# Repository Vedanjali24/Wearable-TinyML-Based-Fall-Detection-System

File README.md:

# Wearable-TinyML-Based-Fall-Detection-System
This project focuses on the design and development of a wearable health monitoring system capable of performing real-time motion analysis and fall detection directly on the device. The system is built around the ESP32 microcontroller, which serves as the main processing unit for sensor data acquisition, TinyML inference, and data logging.

The device integrates an MPU6050 inertial measurement unit (IMU) to capture motion and orientation data and a MAX30102 optical sensor for physiological monitoring such as heart rate and blood oxygen levels. Motion data from the IMU is processed locally using a TinyML model trained for fall detection, allowing the system to identify abnormal movement patterns without requiring external computation resources.

To enable reliable data storage and post-analysis, the system includes SD card logging, where raw sensor readings and detected events are stored during operation. This allows offline analysis of movement patterns, model performance evaluation, and long-term monitoring.

A key objective of the system is privacy-preserving edge intelligence. All inference and decision-making are performed directly on the embedded device, eliminating the need for continuous cloud connectivity. This reduces latency, lowers power consumption, and ensures that sensitive health data remains local to the device.

The combination of embedded machine learning, sensor fusion, and edge processing enables the device to operate as a compact and efficient health monitoring platform capable of detecting potential falls and anomalies in real time.

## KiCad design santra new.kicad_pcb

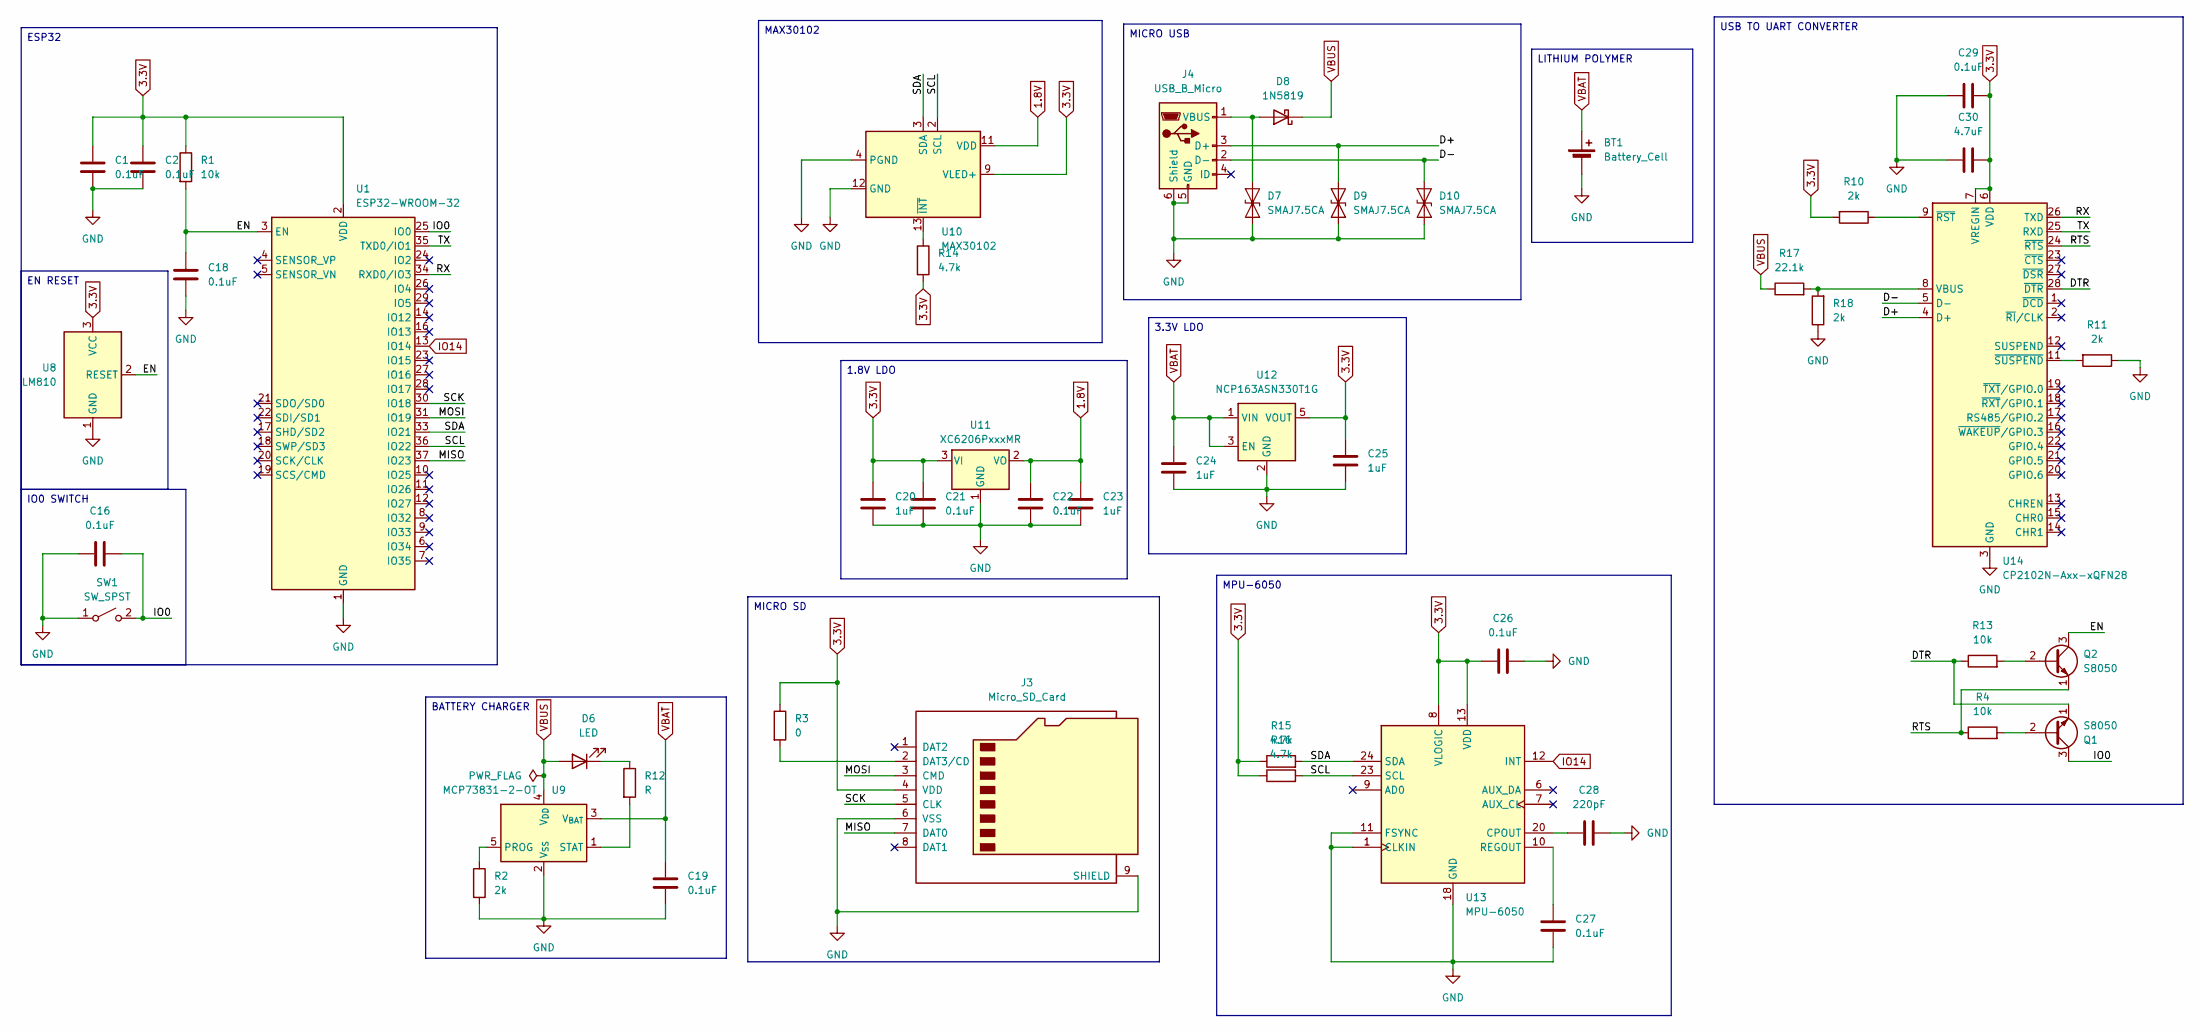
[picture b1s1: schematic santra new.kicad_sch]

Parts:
BT1: Battery_Cell; LED_PLCC-2_3x2mm_AK
C1, C2, C16, C18, C19, C21, C22, C26, C27, C29: 0.1uF; C_0603_1608Metric_Pad1.08x0.95mm_HandSolder
C20, C23, C24, C25: 1uF; C_0603_1608Metric_Pad1.08x0.95mm_HandSolder
C28: 220pF; C_0603_1608Metric_Pad1.08x0.95mm_HandSolder
C30: 4.7uF; C_0603_1608Metric_Pad1.08x0.95mm_HandSolder
D6: LED; LED_0603_1608Metric_Pad1.05x0.95mm_HandSolder
D7, D9, D10: SMAJ7.5CA; D_SMA
D8: 1N5819; D_DO-41_SOD81_P10.16mm_Horizontal
J3: Micro_SD_Card; microSD_HC_Molex_47219-2001
J4: USB_B_Micro; USB_Micro-B_Molex-105017-0001
Q1, Q2: S8050; Texas_DRT-3
R1, R4, R13: 10k; R_0603_1608Metric_Pad0.98x0.95mm_HandSolder
R2, R10, R11, R18: 2k; R_0603_1608Metric_Pad0.98x0.95mm_HandSolder
R3: 0; R_0603_1608Metric_Pad0.98x0.95mm_HandSolder
R12: R; R_0603_1608Metric_Pad0.98x0.95mm_HandSolder
R14, R15, R16: 4.7k; R_0603_1608Metric_Pad0.98x0.95mm_HandSolder
R17: 22.1k; R_0603_1608Metric_Pad0.98x0.95mm_HandSolder
SW1: SW_SPST; SW_Push_1P1T_NO_CK_PTS125Sx43PSMTR
U1: ESP32-WROOM-32
U8: LM810; SOT-23
U9: MCP73831-2-OT; SOT-23-5
U10: MAX30102; Maxim_OLGA-14_3.3x5.6mm_P0.8mm
U11: XC6206PxxxMR; SOT-23-3
U12: NCP163ASN330T1G; SOT-23-5
U13: MPU-6050; InvenSense_QFN-24_4x4mm_P0.5mm
U14: CP2102N-Axx-xQFN28; QFN-28-1EP_5x5mm_P0.5mm_EP3.35x3.35mm

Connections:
1.8V: C22.1, C23.1, U10.11 (VDD), U11.2 (VO)
3.3V: C1.1, C2.1, C20.1, C21.1, C25.1, C26.1, C29.2, C30.2, J3.4 (VDD), R1.1, R3.1, R10.2, R14.2, R15.1, R16.1, U1.2 (VDD), U8.3 (VCC), U10.9 (VLED+), U10.10 (VLED+), U11.3 (VI), U12.5 (VOUT), U13.8 (VLOGIC), U13.13 (VDD), U14.6 (VDD), U14.7 (VREGIN)
/D+: D9.2 (A2), J4.3 (D+), U14.4 (D+)
/D-: D10.2 (A2), J4.2 (D-), U14.5 (D-)
/DTR: Q1.1 (E), R13.1, U14.28 (~DTR)
/EN: C18.1, Q2.3 (C), R1.2, U1.3 (EN), U8.2 (RESET)
/IO0: C16.2, Q1.3 (C), SW1.2 (B), U1.25 (IO0)
/MISO: J3.7 (DAT0), U1.37 (IO23)
/MOSI: J3.3 (CMD), U1.31 (IO19)
/RTS: Q2.1 (E), R4.1, U14.24 (~RTS)
/RX: U1.34 (RXD0/IO3), U14.26 (TXD)
/SCK: J3.5 (CLK), U1.30 (IO18)
/SCL: R16.2, U1.36 (IO22), U10.2 (SCL), U13.23 (SCL)
/SDA: R15.2, U1.33 (IO21), U10.3 (SDA), U13.24 (SDA)
/TX: U1.35 (TXD0/IO1), U14.25 (RXD)
GND: BT1.2 (-), C1.2, C2.2, C16.1, C18.2, C19.2, C20.2, C21.2, C22.2, C23.2, C24.2, C25.2, C26.2, C27.2, C28.2, C29.1, C30.1, D7.1 (A1), D9.1 (A1), D10.1 (A1), J3.6 (VSS), J3.9 (SHIELD), J4.5 (GND), J4.6 (Shield), R2.2, R11.1, R18.1, SW1.1 (A), U1.1 (GND), U1.15 (GND), U1.38 (GND), U1.39 (GND), U8.1 (GND), U9.2 (V_{SS}), U10.4 (PGND), U10.12 (GND), U11.1 (GND), U12.2 (GND), U13.1 (CLKIN), U13.11 (FSYNC), U13.18 (GND), U14.3 (GND), U14.29 (GND)
IO14: U1.13 (IO14), U13.12 (INT)
unnamed: D6.1 (K), R12.1
unnamed: D7.2 (A2), D8.2 (A), J4.1 (VBUS)
unnamed: J3.2 (DAT3/CD), R3.2
unnamed: Q1.2 (B), R4.2
unnamed: Q2.2 (B), R13.2
unnamed: R2.1, U9.5 (PROG)
unnamed: R12.2, U9.1 (STAT)
unnamed: R14.1, U10.13 (~INT)
unnamed: C28.1, U13.20 (CPOUT)
unnamed: C27.1, U13.10 (REGOUT)
unnamed: R17.2, R18.2, U14.8 (VBUS)
unnamed: R10.1, U14.9 (~RST)
unnamed: R11.2, U14.11 (~SUSPEND)
VBAT: BT1.1 (+), C19.1, C24.1, U9.3 (V_{BAT}), U12.1 (VIN), U12.3 (EN)
VBUS: D6.2 (A), D8.1 (K), R17.1, U9.4 (V_{DD})

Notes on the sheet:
MICRO SD
3.3V LDO
LITHIUM POLYMER
USB TO UART CONVERTER
1.8V LDO
BATTERY CHARGER
MPU-6050
IO0 SWITCH
EN RESET
ESP32
MICRO USB
MAX30102

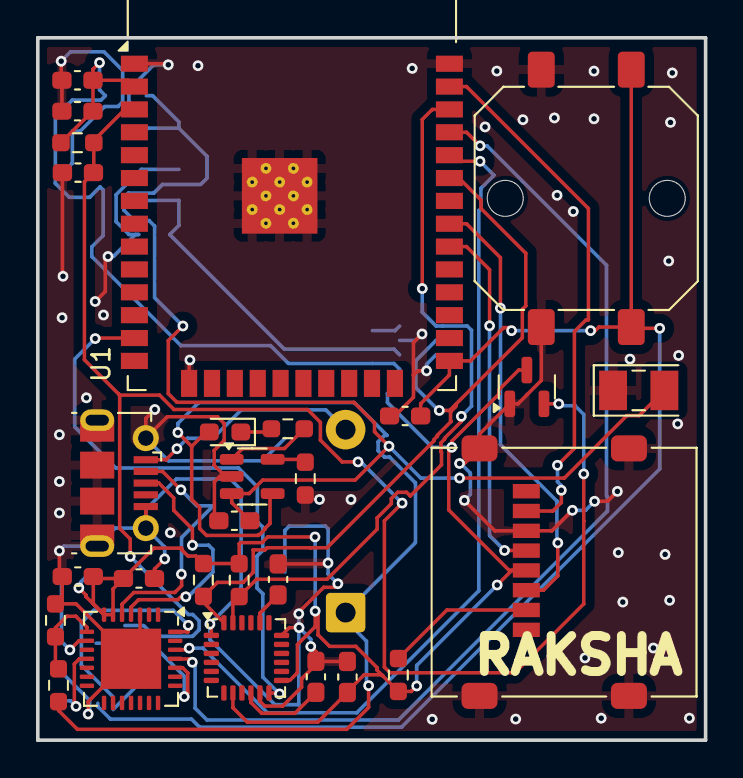
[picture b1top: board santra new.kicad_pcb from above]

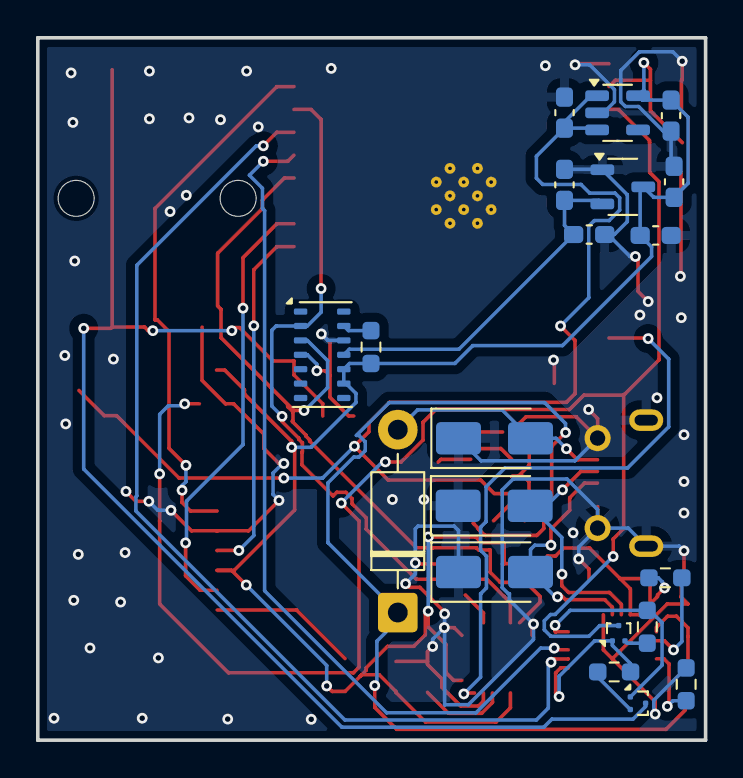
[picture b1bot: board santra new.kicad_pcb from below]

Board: 2 copper layers, 37.1 x 39.0 mm, 48 parts (20 on the bottom side), 32 nets.

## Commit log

2026-03-10 Enhance README with detailed project overview
    Expanded project description to detail system components, functionality, and privacy features.
2026-03-10 Add image to README for better visual representation
    Added an image to enhance the README with visual content.
